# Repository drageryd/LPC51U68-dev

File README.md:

# LPC51u68 development board

This chip has 8 general purpose serial peripherals that can be used
for UART, I2C or SPI. All packed in a relatively small 48 pin LQFP
package.

The board is designed in KiCad and will fit a standard breadboard.

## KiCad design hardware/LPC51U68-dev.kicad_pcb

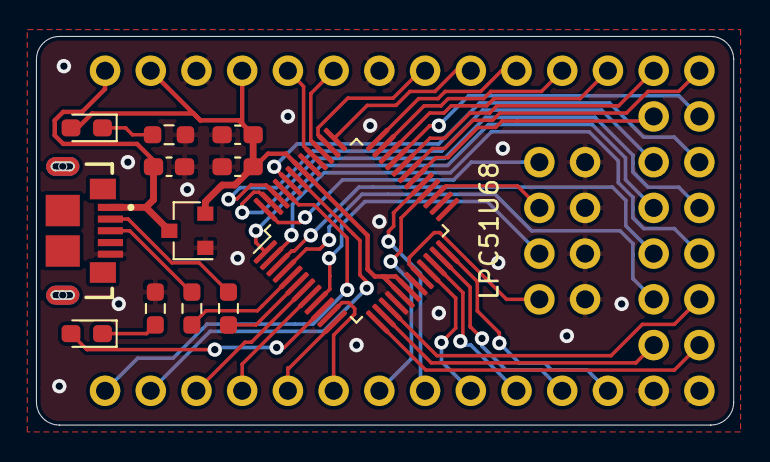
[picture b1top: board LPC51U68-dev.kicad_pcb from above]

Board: 2 copper layers, 38.7 x 21.5 mm, 24 parts (0 on the bottom side), 47 nets.

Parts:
C2: 100n; C_0603_1608Metric_Pad1.08x0.95mm_HandSolder
C4, C5: 1u; C_0603_1608Metric_Pad1.08x0.95mm_HandSolder
D1, D2: LED; LED_0603_1608Metric_Pad1.05x0.95mm_HandSolder
J1: Conn_02x04_Odd_Even; PinHeader_2x04_P2.54mm_Vertical
J2, J7: Conn_01x04; PinHeader_1x04_P2.54mm_Vertical
J6: Conn_02x06_Odd_Even; PinHeader_2x06_P2.54mm_Vertical
J8, J9, J10, J11, J12, J13: Conn_01x02; PinHeader_1x02_P2.54mm_Vertical
J14: Conn_01x05; PinHeader_1x05_P2.54mm_Vertical
J15: USB_B_Micro; GCT_USB3076-XX-X_REVC
J16: Conn_01x03; PinHeader_1x03_P2.54mm_Vertical
R1, R2: 100R; R_0603_1608Metric_Pad0.98x0.95mm_HandSolder
R3, R4: 33R; R_0603_1608Metric_Pad0.98x0.95mm_HandSolder
U1: lpc51u68; LQFP-48_7x7mm_P0.5mm
U2: MCP1703A-3302_SOT23; SOT-23

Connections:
+3V3: C2.1, C5.1, D2.2, J2.4, J16.2, U1.17, U1.18, U1.42, U2.2
/FC0_RXD_SDA: J7.4, U1.23
/FC0_TXD_SCL: J7.3, U1.24
/FC1_RXD_SDA: J8.1, U1.7
/FC1_TXD_SCL: J8.2, U1.8
/FC2_RXD_SDA: J9.1, U1.31
/FC2_TXD_SCL: J9.2, U1.32
/FC3_CTS_SDA_SSEL0: J14.2, U1.37
/FC3_RTS_SCL_SSEL1: J14.1, U1.38
/FC3_RXD_SDA_MOSI: J14.4, U1.35
/FC3_SCK: J14.5, U1.34
/FC3_TXD_SCL_MISO: J14.3, U1.36
/FC4_RXD_SDA: J10.1, U1.12
/FC4_TXD_SCL: J10.2, U1.11
/FC5_RXD_SDA: J11.1, U1.45
/FC5_TXD_SCL: J11.2, U1.43
/FC6_RXD_SDA: J12.1, U1.28
/FC6_TXD_SCL: J12.2, U1.29
/FC7_RXD_SDA: J13.1, U1.21
/FC7_TXD_SCL: J13.2, U1.22
/ISP0: J1.5, U1.9
/ISP1: J1.3, U1.27
/ISP_VBUS: J1.7, U1.20
/LED: D1.2, U1.10
/PIO0_7: J6.12, U1.30
/PIO0_10: J6.11, U1.33
/PIO0_19: J6.9, U1.44
/PIO0_21: J6.10, U1.46
/PIO0_22: J6.7, U1.47
/PIO0_23: J6.8, U1.1
/PIO0_24: J6.5, U1.2
/PIO0_25: J6.6, U1.3
/PIO0_26: J6.4, U1.4
/PIO1_3: J6.1, U1.13
/PIO1_4: J6.2, U1.14
/PIO1_5: J6.3, U1.15
/SWDCLK: J2.2, U1.39
/SWDIO: J2.3, U1.40
/USB_DM: R4.1, U1.6
/USB_DP: R3.1, U1.5
/~RESET: J1.1, U1.48
GND: C2.2, C4.2, C5.2, J1.2, J1.4, J1.6, J1.8, J2.1, J7.1, J7.2, J15.5, J16.1, R1.2, R2.2, U1.16, U1.19, U1.41, U2.1
unnamed: D1.1, R1.1
unnamed: D2.1, R2.1
unnamed: J15.2, R4.2
unnamed: J15.3, R3.2
VBUS: C4.1, J15.1, J16.3, U2.3

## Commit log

2022-03-04 Inital board design
2022-03-04 Gerber files for initial prototype
2022-03-04 Rename pcb directory to hardware and move KiCad gitignore there
2022-03-04 Import LPC51U68 MCUXpresso SDK archive
2022-03-04 Add some makefile scaffolding
2022-03-10 Initial makefiles to build a simple blink example
    - Build some SDK source files needed for GPIO
    - Build minimal blink example
    - Link and create .bin and .hex files
    - Flash using JLink
2023-05-09 Add license
